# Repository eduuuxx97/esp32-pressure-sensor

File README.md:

# ESP32 Pressure Sensor

Sistema de aquisição de dados IoT multicanal para monitoramento remoto de pressão e temperatura, desenvolvido com ESP32, conversores ADC externos ADS1115 e sensores industriais de pressão em malha de corrente 4–20 mA.

Este projeto foi desenvolvido como parte de um Trabalho de Conclusão de Curso em Engenharia Eletrônica, com aplicação no monitoramento de ensaios laboratoriais envolvendo pressão e temperatura em experimentos de produção de biometano.

## Visão Geral

O sistema realiza a leitura de até seis canais de pressão e um canal de temperatura, processando os sinais em um microcontrolador ESP32. As leituras são disponibilizadas por uma interface web local e podem ser acompanhadas por uma aplicação supervisória para Windows, responsável pela visualização e armazenamento dos dados em arquivo CSV.

A cadeia de aquisição dos canais de pressão é baseada em sensores industriais com saída de corrente de 4–20 mA. A corrente é convertida em tensão por meio de resistores shunt e posteriormente digitalizada por conversores ADS1115. No firmware, os dados são filtrados e convertidos para valores de pressão em unidade de engenharia.

## Funcionalidades

* Leitura de seis canais analógicos de pressão;
* Leitura de temperatura por sensor digital;
* Conversão de sinais 4–20 mA para pressão em bar;
* Filtragem digital das leituras;
* Comunicação Wi-Fi com interface web;
* Aplicação supervisória para Windows;
* Salvamento local dos dados em CSV;
* Projeto de hardware/PCB versionado junto ao firmware;
* Organização modular do firmware embarcado.

## Tecnologias Utilizadas

### Firmware

* ESP32;
* PlatformIO;
* Arduino Framework;
* Linguagem C/C++;
* Comunicação I2C;
* Conversores ADS1115;
* Sensor de temperatura DS18B20.

### Aplicação Supervisória

* Python;
* pywebview;
* requests;
* csv;
* threading.

### Hardware

* KiCad;
* Sensores industriais de pressão 4–20 mA;
* Resistores shunt;
* Conversores ADS1115;
* Módulo RTC;
* Módulo cartão SD;
* ESP32 DevKit.

## Estrutura do Repositório

```text
esp32-pressure-sensor/
├── App_PC/                  # Aplicação supervisória para Windows
├── Hardware/                # Projeto da PCB e arquivos de hardware
├── include/                 # Arquivos de cabeçalho do firmware
├── lib/                     # Bibliotecas internas do projeto
│   └── SensorLib/           # Biblioteca de aquisição e conversão dos sensores
├── src/                     # Código principal do firmware
├── platformio.ini           # Configuração do PlatformIO
├── .gitignore               # Arquivos ignorados pelo Git
└── README.md                # Documentação principal do projeto
```

## Conversão dos Sensores de Pressão

Os sensores de pressão utilizados trabalham com saída de corrente na faixa de 4–20 mA. A corrente da malha é convertida em tensão por meio de um resistor shunt de 150 ohms.

No firmware, a corrente é calculada pela relação:

```cpp
float corrente_mA = (adc_filtrado[i] / R_SHUNT) * 1000.0;
```

Em seguida, a pressão é obtida por interpolação linear entre os limites do sensor:

```cpp
pressoes_finais[i] = PRESSAO_MIN + 
                     (corrente_mA - 4.0) * 
                     (PRESSAO_MAX - PRESSAO_MIN) / 16.0;
```

Para os sensores utilizados neste projeto:

```cpp
static const float R_SHUNT = 150.0;
static const float PRESSAO_MIN = 0.5;
static const float PRESSAO_MAX = 3.0;
```

Assim, a conversão considera:

```text
4 mA  -> 0,5 bar
20 mA -> 3,0 bar
```

## Aplicação Supervisória

A aplicação localizada em `App_PC/` utiliza Python e pywebview para abrir a interface web servida pelo ESP32 em uma janela desktop.

O ESP32 disponibiliza a interface localmente, e a aplicação supervisória acessa o endereço:

```text
http://192.168.4.1
```

Além da visualização, a aplicação realiza a coleta periódica dos dados e o salvamento em arquivo CSV no computador.

## Como Executar o Firmware

1. Clone o repositório:

```bash
git clone https://github.com/eduuuxx97/esp32-pressure-sensor.git
```

2. Acesse a pasta do projeto:

```bash
cd esp32-pressure-sensor
```

3. Abra o projeto no VS Code com PlatformIO.

4. Compile o firmware:

```bash
pio run
```

5. Envie o firmware para o ESP32:

```bash
pio run --target upload
```

6. Abra o monitor serial:

```bash
pio device monitor
```

## Como Executar a Aplicação do PC

Acesse a pasta da aplicação:

```bash
cd App_PC
```

Instale as dependências necessárias:

```bash
pip install pywebview requests
```

Execute a aplicação:

```bash
python MonitorApp.py
```

## Hardware

Os arquivos do projeto da placa de circuito impresso estão disponíveis na pasta:

```text
Hardware/
```

Essa pasta contém o projeto desenvolvido no KiCad, incluindo esquemático, layout da PCB, bibliotecas de símbolos, footprints e arquivos de fabricação.

## Observações

* Os arquivos temporários, backups e ambientes virtuais não são versionados no repositório.
* O projeto utiliza conversores ADS1115 para aumentar a resolução das leituras analógicas em relação ao ADC interno do ESP32.
* A calibração experimental pode ser ajustada no firmware conforme os dados obtidos em bancada com instrumento de referência.

## Autor

Eduardo dos Santos Rodrigues
Engenharia Eletrônica — Universidade Federal de Pernambuco

GitHub: [@eduuuxx97](https://github.com/eduuuxx97)

## Repositório

Este projeto está disponível em:

```text
https://github.com/eduuuxx97/esp32-pressure-sensor
```

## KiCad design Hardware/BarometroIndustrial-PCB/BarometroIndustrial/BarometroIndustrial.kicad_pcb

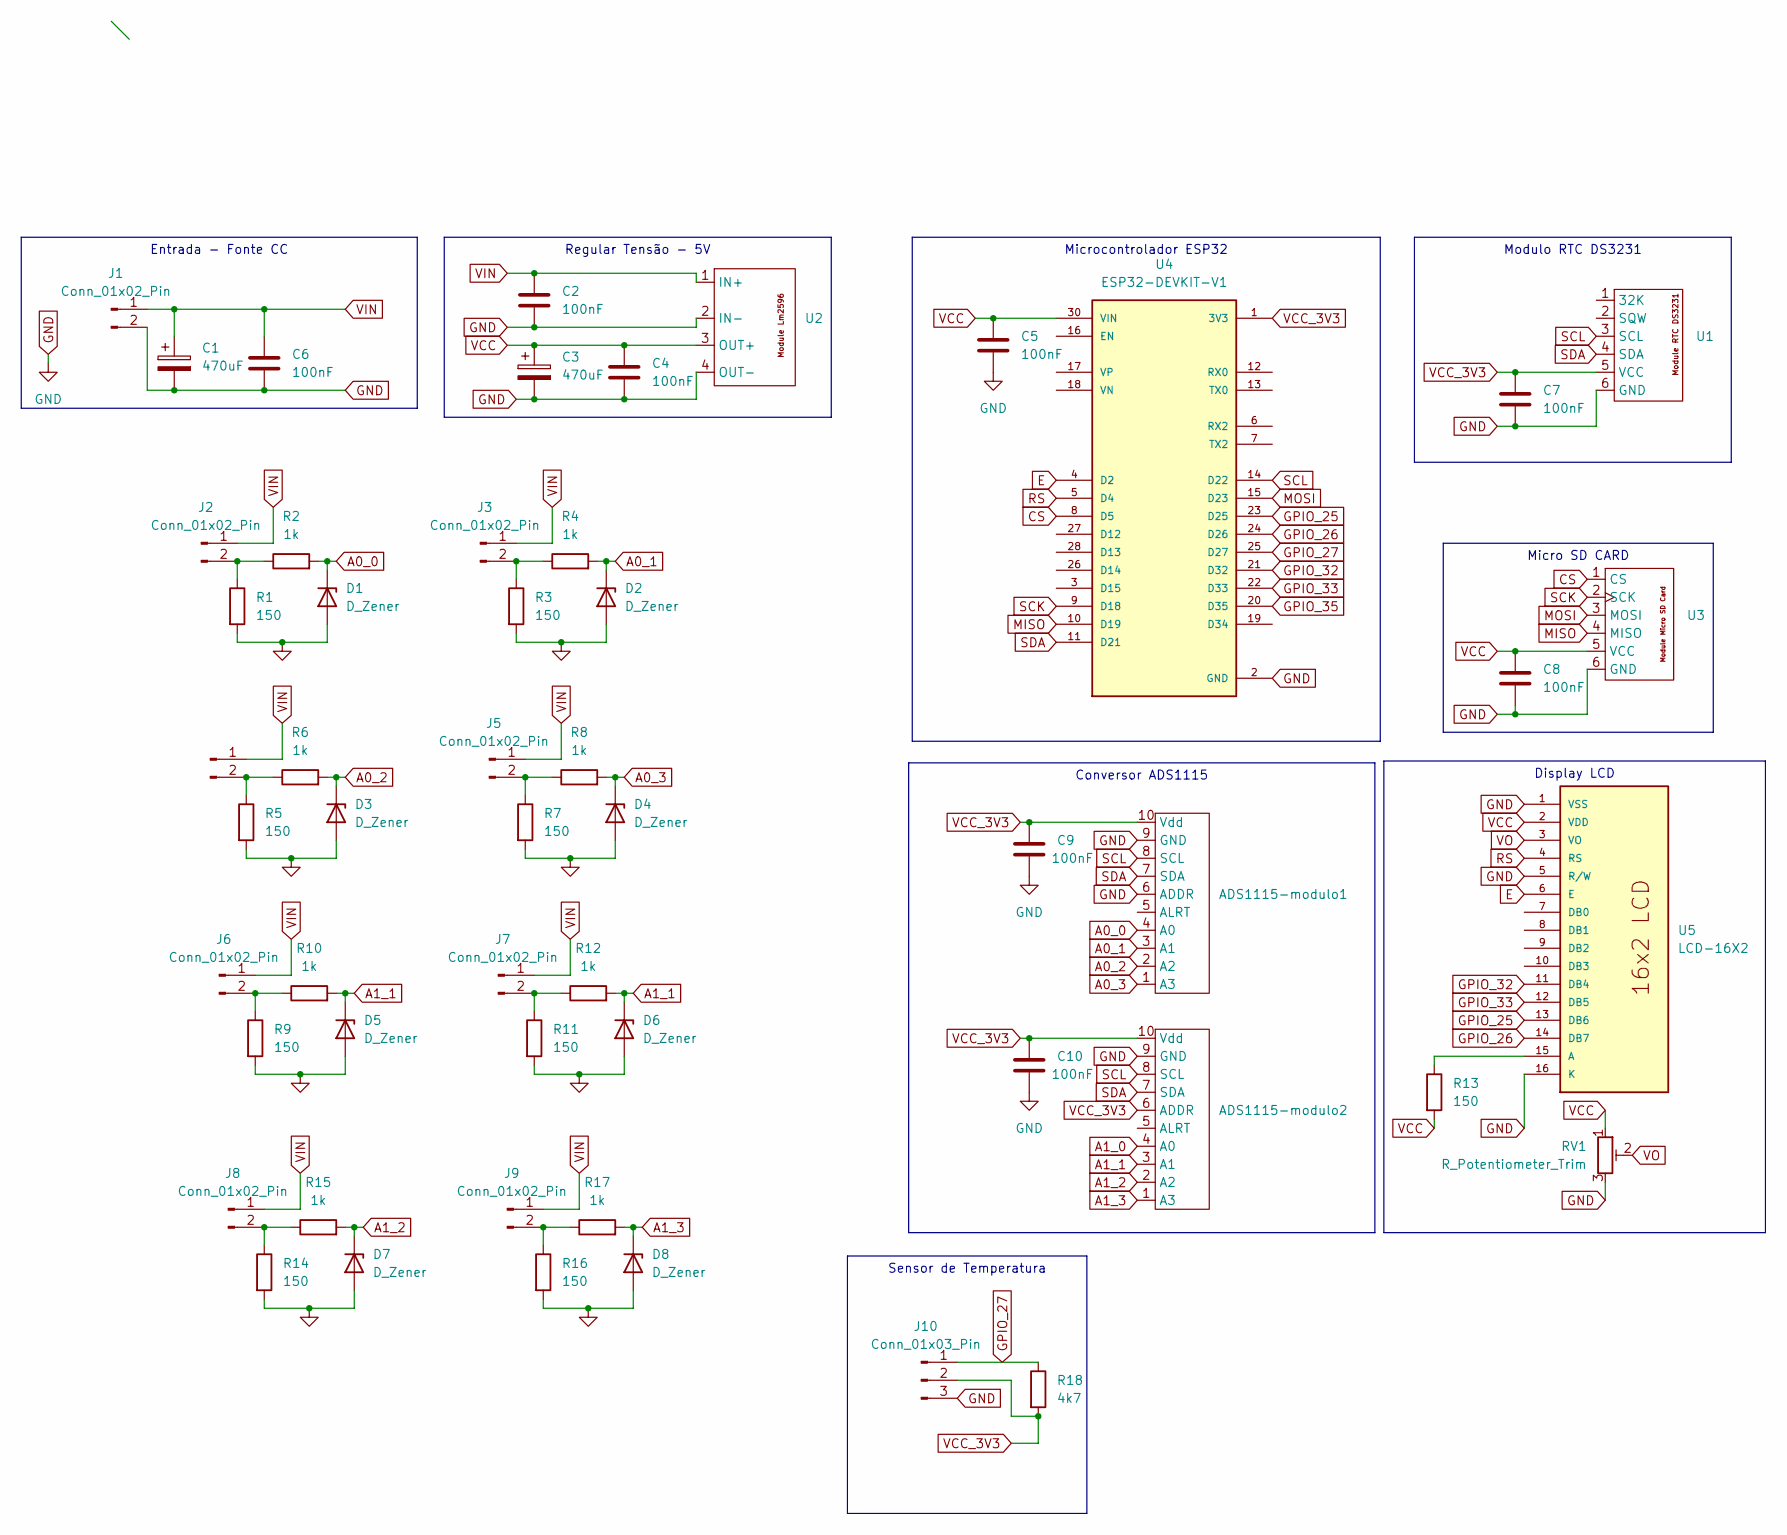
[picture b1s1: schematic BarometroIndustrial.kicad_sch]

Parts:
ADS1115-modulo1, ADS1115-modulo2: ADS1115-module
C1, C3: 470uF; CP_Radial_D10.0mm_P2.50mm
C2, C4, C5, C6, C7, C8, C9, C10: 100nF; C_Disc_D5.0mm_W2.5mm_P5.00mm
D1, D2, D3, D4, D5, D6, D7, D8: D_Zener; D_DO-35_SOD27_P10.16mm_Horizontal
J1, J2, J3, J5, J6, J7, J8, J9: Conn_01x02_Pin; TerminalBlock_MaiXu_MX126-5.0-02P_1x02_P5.00mm
J4: Entrada do Sensor de Pressão; TerminalBlock_MaiXu_MX126-5.0-02P_1x02_P5.00mm
J10: Conn_01x03_Pin; PinHeader_1x03_P2.54mm_Vertical
R1, R3, R5, R7, R9, R11, R14, R16: 150; R_Axial_DIN0309_L9.0mm_D3.2mm_P12.70mm_Horizontal
R2, R4, R6, R8, R10, R12, R15, R17: 1k; R_Axial_DIN0309_L9.0mm_D3.2mm_P12.70mm_Horizontal
R13: 150; R_Axial_DIN0309_L9.0mm_D3.2mm_P5.08mm_Vertical
R18: 4k7; R_Axial_DIN0309_L9.0mm_D3.2mm_P12.70mm_Horizontal
RV1: R_Potentiometer_Trim; Potentiometer_Bourns_3296W_Vertical
U1: RTCDS3231
U2: LM2596StepDown
U3: MicroSD
U4: ESP32-DEVKIT-V1; MODULE_ESP32_DEVKIT_V1; PARTREV N/A
U5: LCD-16X2; PinHeader_1x16_P2.54mm_Vertical; PARTREV N/A

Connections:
A0_0: ADS1115-modulo1.4 (A0), D1.1 (K), R2.2
A0_1: ADS1115-modulo1.3 (A1), D2.1 (K), R4.2
A0_2: ADS1115-modulo1.2 (A2), D3.1 (K), R6.2
A0_3: ADS1115-modulo1.1 (A3), D4.1 (K), R8.2
A1_2: ADS1115-modulo2.2 (A2), D7.1 (K), R15.2
A1_3: ADS1115-modulo2.1 (A3), D8.1 (K), R17.2
CS: U3.1 (CS), U4.8 (D5)
E: U4.4 (D2), U5.6 (E)
GND: ADS1115-modulo1.6 (ADDR), ADS1115-modulo1.9 (GND), ADS1115-modulo2.9 (GND), C1.2, C2.2, C3.2, C4.2, C5.2, C6.2, C7.2, C8.2, C9.2, C10.2, D1.2 (A), D2.2 (A), D3.2 (A), D4.2 (A), D5.2 (A), D6.2 (A), D7.2 (A), D8.2 (A), J1.2, J10.3, R1.2, R3.2, R5.2, R7.2, R9.2, R11.2, R14.2, R16.2, RV1.3, U1.6 (GND), U2.2 (IN-), U2.4 (OUT-), U3.6 (GND), U4.2 (GND), U4.29 (GND), U5.1 (VSS), U5.5 (R/W), U5.16 (K)
GPIO_25: U4.23 (D25), U5.13 (DB6)
GPIO_26: U4.24 (D26), U5.14 (DB7)
GPIO_27: J10.1, R18.1, U4.25 (D27)
GPIO_32: U4.21 (D32), U5.11 (DB4)
GPIO_33: U4.22 (D33), U5.12 (DB5)
GPIO_35: U4.20 (D35)
MISO: U3.4 (MISO), U4.10 (D19)
MOSI: U3.3 (MOSI), U4.15 (D23)
unnamed: J2.2, R1.1, R2.1
unnamed: J3.2, R3.1, R4.1
unnamed: J4.2, R5.1, R6.1
unnamed: J5.2, R7.1, R8.1
unnamed: J6.2, R9.1, R10.1
unnamed: J7.2, R11.1, R12.1
unnamed: J8.2, R14.1, R15.1
unnamed: J9.2, R16.1, R17.1
unnamed: R13.1, U5.15 (A)
RS: U4.5 (D4), U5.4 (RS)
SCK: U3.2 (SCK), U4.9 (D18)
SCL: ADS1115-modulo1.8 (SCL), ADS1115-modulo2.8 (SCL), U1.3 (SCL), U4.14 (D22)
SDA: ADS1115-modulo1.7 (SDA), ADS1115-modulo2.7 (SDA), U1.4 (SDA), U4.11 (D21)
VCC: C3.1, C4.1, C5.1, C8.1, R13.2, RV1.1, U2.3 (OUT+), U3.5 (VCC), U4.30 (VIN), U5.2 (VDD)
VCC_3V3: ADS1115-modulo1.10 (Vdd), ADS1115-modulo2.6 (ADDR), ADS1115-modulo2.10 (Vdd), C7.1, C9.1, C10.1, J10.2, R18.2, U1.5 (VCC), U4.1 (3V3)
VIN: C1.1, C2.1, C6.1, J1.1, J2.1, J3.1, J4.1, J5.1, J6.1, J7.1, J8.1, J9.1, U2.1 (IN+)
VO: RV1.2, U5.3 (VO)

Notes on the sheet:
Sensor de Temperatura
Regular Tensão - 5V
Modulo RTC DS3231
Micro SD CARD
Display LCD
Conversor ADS1115
Microcontrolador ESP32
Entrada - Fonte CC

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
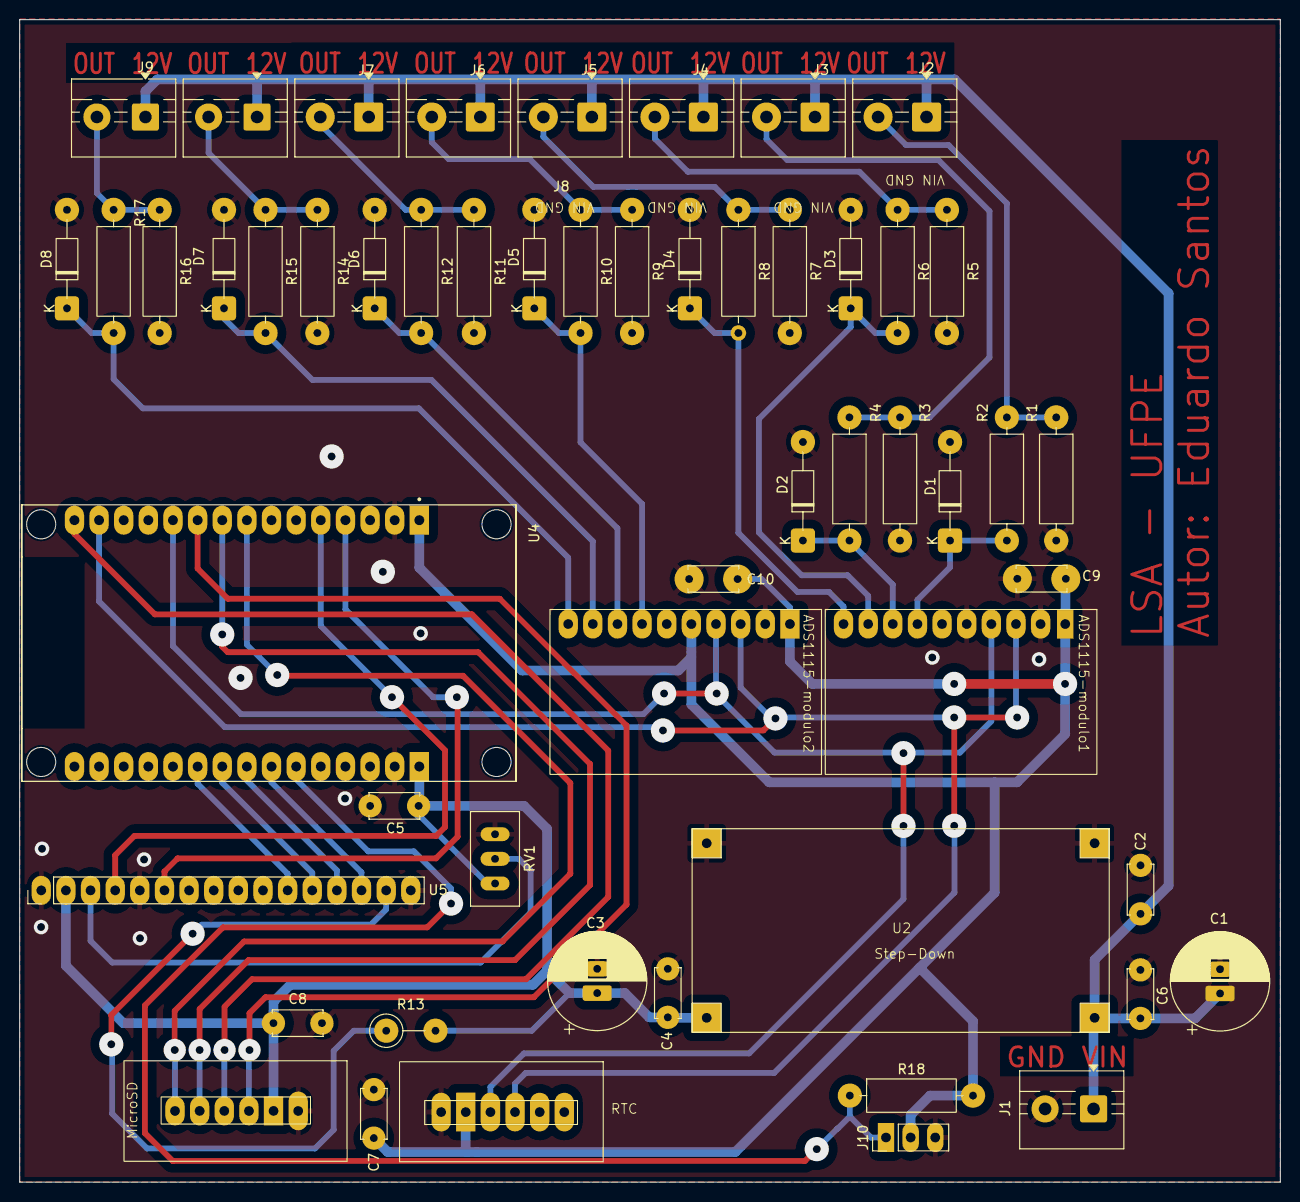
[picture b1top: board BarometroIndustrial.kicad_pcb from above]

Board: 2 copper layers, 130.0 x 119.9 mm, 54 parts (0 on the bottom side), 35 nets.

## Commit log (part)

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2025-12-11 Primeiro Commit
2025-12-11 Adiciona filro exponencial para estabilizar leitura
2025-12-11 Codigo exponencial para leitura de 6 sensores
2025-12-11 Adciona gráfico em tempo real e corrige senha wifi
2025-12-22 Finaliza Fase 1: Arquitetura modular, Grafico Web e SD Card funcionando
2026-02-03 Versão estável: SD e Python gravando sincronizados
2026-02-12 Versão corrigida de queda de energia + conexão da interface automática com o esp32
2026-02-12 LEDs de status e o botão de Reset para controle visual
2026-02-13 I2C com WatchDog - Versão Final
2026-02-15 Adicionado Coluna de falta de LUZ - Versão Final
2026-03-09 Finalizada a resiliência de log, recuperação de intervalo e sensor de temperatura- Final
2026-03-30 Inserir eixo X e Y. Eixo Y=Pressão e Eixo X=Tempo
2026-06-26 Correção do offset - O sensor não captura mais a pressão atmosférica
2026-06-26 adiciona projeto de hardware da PCB
2026-06-26 atualiza conversao dos sensores de pressao
